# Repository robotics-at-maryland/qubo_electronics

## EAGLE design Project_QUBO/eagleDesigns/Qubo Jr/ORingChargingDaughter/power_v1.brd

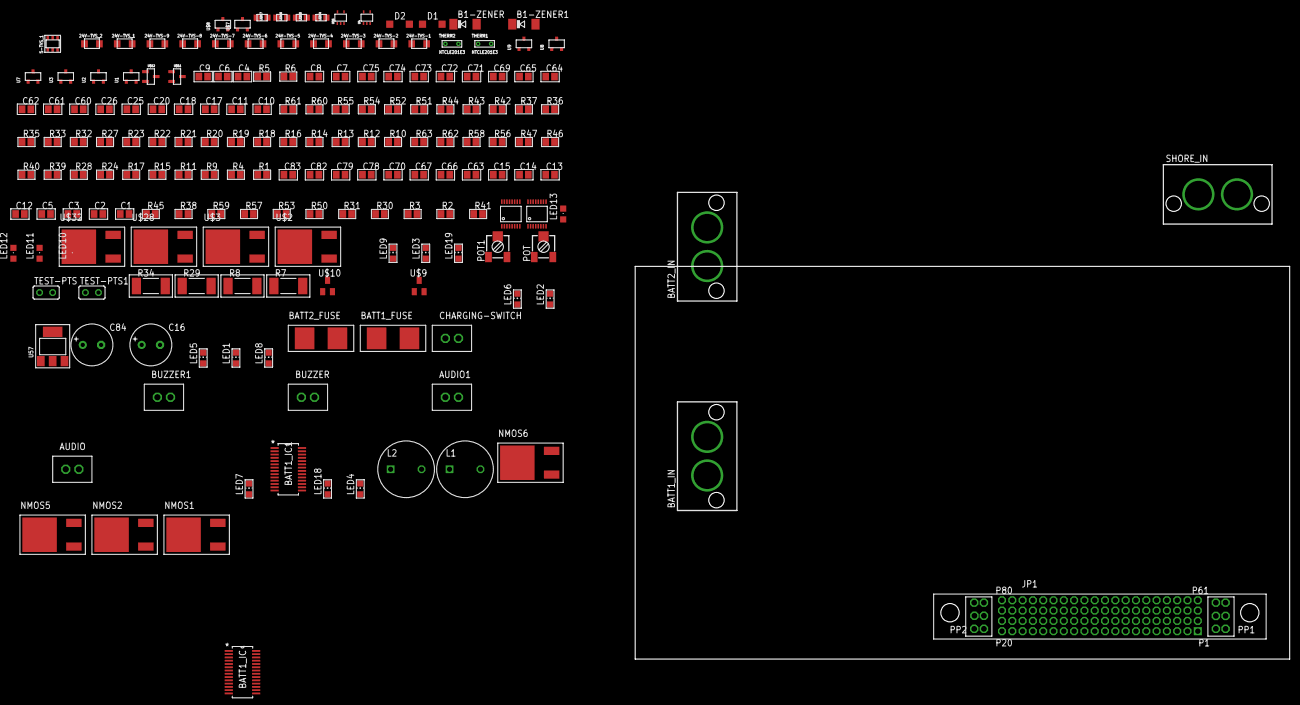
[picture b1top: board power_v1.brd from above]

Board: 2 copper layers, 127.0 x 76.2 mm, 181 parts (0 on the bottom side), 115 nets, no tracks yet.

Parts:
5-TVS_1: BZA408B; SOT457
24V-TVS-1, 24V-TVS-2, 24V-TVS-3, 24V-TVS-4, 24V-TVS-5, 24V-TVS-6, 24V-TVS-7, 24V-TVS-8, 24V-TVS-9, 24V-TVS_1, 24V-TVS_2: VTVS; DO-219AB
AUDIO, AUDIO1: KK254_VERT_2PIN22-29-2021; KK254_VERT_2PIN
B1-ZENER, B1-ZENER1: SOD106-R
BATT1_FUSE, BATT2_FUSE: 4A; 154-OMNI-BLOK
BATT1_IC, BATT1_IC1: MAX1737; QSOP28
BATT1_IN, BATT2_IN: 2_SUPERSABRE; SUPERSABRE_2CIRCUIT
BUZZER, BUZZER1: KK254_VERT_2PIN22-29-2021; KK254_VERT_2PIN
C1, C5, C12, C13, C14, C15, C63, C70, C78, C79, C82, C83: 0.1u; C0805
C2, C3, C66, C67: 2.2u; C0805
C4, C60, C69: 1u; C0805
C6, C9, C10, C71, C74, C75: 1n; C0805
C7, C8, C17, C64, C72, C73: 47n; C0805
C11, C20, C25, C26: 0.1; C0805
C16, C84: 120u; E3,5-8
C18, C65: 22u; C0805
C61, C62: 10u; C0805
CHARGING-SWITCH: KK254_VERT_2PIN22-29-2021; KK254_VERT_2PIN
D1, D2: SOD123
JP1: MPSC-01-80
L1, L2: 10uH; L6100
LED1, LED5: FASTCHG; CHIP-LED0805
LED2, LED6: FULLCHG; CHIP-LED0805
LED3, LED9: FAULT; CHIP-LED0805
LED4, LED18: Batt Connect.; CHIP-LED0805
LED7: Shore Power; CHIP-LED0805
LED8: CHARGING; CHIP-LED0805
LED10, LED11: Red; CHIPLED_0805
LED12, LED13: CHIPLED_0805
LED14, LED15: Blue; 0805
LED16, LED17: Green; 0805
LED19: ORING; CHIP-LED0805
NMOS1, NMOS2, NMOS5, NMOS6: STD95N2LH5; DPAK
POT, POT1: 10k; RTRIM3314J
R1, R4: 2-3k; R0805
R2, R3, R30, R31: ~50k; R0805
R5, R32: 10k; R0805
R6, R33, R52, R55, R60, R61: 330; R0805
R7, R8, R29, R34: 100m; R2512
R9, R11, R15, R17, R56, R58: 1.2k; R0805
R10, R12, R14, R16, R18, R20: 50k; R0805
R13, R21, R23: 510; R0805
R19, R22: 680; R0805
R24: 6.8k; R0805
R27: 12k; R0805
R28, R62, R63: 1.5k; R0805
R35, R42: 51k; R0805
R36, R43: 5m; R0805
R37, R44: 10\; R0805
R38, R45: 200k; R0805
R39, R46: 8.2k; R0805
R40, R47: 5.1k; R0805
R41: 20.8k; R0805
R50, R53, R57, R59: 20k+; R0805
R51, R54: 430; R0805
SHORE_IN: 2_SUPERSABRE; SUPERSABRE_2CIRCUIT
TEST-PTS, TEST-PTS1: 0; V526-0
THERM1, THERM2: NTCLE201E3; 2-0.3MM-LEADS
U1, U2, U3, U7, U8, U9: SSM3J353F; SOT-346-3/S-MINI
U4, U56: 74LVC1G14; TSSOP5
U57: NCP1117; SOT-223
U$1, U$27: LTC4364MSOP; MSOP16
U$2, U$3, U$28, U$32: STD95N2LH5; DPAK
U$7, U$8: SSM3J353F; SOT-346-3/S-MINI
U$9, U$10: BSS138CT-NDSOT23; SOT23
U$11, U$12: TL431DBZ; SOT-23-3

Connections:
+5V: C11.1, C20.1, C62.1, R24.2, U4.P$5, U56.P$5, U57.P$2, U57.P$4
BATT1_P: 24V-TVS_2.P$2, BATT1_FUSE.P$1, BATT1_IN.P$1
BATT2_P: 24V-TVS-3.P$2, BATT2_FUSE.P$1, BATT2_IN.P$1
BATT_1: BATT1_FUSE.P$2, BATT1_IC.7, C83.1, C84.+, R29.1, R34.1
BATT_2: BATT1_IC1.7, BATT2_FUSE.P$2, C15.1, C16.+, R7.1, R8.1
CCI_1: BATT1_IC.11, C72.1
CCI_2: BATT1_IC1.11, C7.1
CCS_1: BATT1_IC.10, C73.1
CCS_2: BATT1_IC1.10, C8.1
CCV_1: BATT1_IC.9, C71.1, R32.2
CCV_2: BATT1_IC1.9, C6.1, R5.2
CHARGE1_!FASTCHG!: BATT1_IC.16, R10.1, U7.P$1
CHARGE1_!FAULT!: BATT1_IC.15, R14.1, U9.P$1
CHARGE1_!FULLCHG!: BATT1_IC.17, R12.1, U8.P$1
CHARGE2_!FASTCHG!: BATT1_IC1.16, R16.1, U1.P$1
CHARGE2_!FAULT!: BATT1_IC1.15, R20.1, U3.P$1
CHARGE2_!FULLCHG!: BATT1_IC1.17, R18.1, U2.P$1
CHARGE-SWT: 5-TVS_1.P$1, CHARGING-SWITCH.P$1, R23.1, R24.1
CHARGE_!SHDN!: BATT1_IC.18, BATT1_IC1.18, R33.2, U4.P$2, U56.P$4
DCIN_1: B1-ZENER.C, BATT1_IC.26, BATT1_IC.27, BATT1_IC.28, C63.1, NMOS1.TAB
DCIN_2: B1-ZENER1.C, BATT1_IC1.26, BATT1_IC1.27, BATT1_IC1.28, C1.1, NMOS5.TAB
DHI1: BATT1_IC.25, NMOS1.1
DHI2: BATT1_IC1.25, NMOS5.1
DLO1: BATT1_IC.21, NMOS2.1
DLO2: BATT1_IC1.21, NMOS6.1
GND: 5-TVS_1.P$2, 24V-TVS-1.P$1, 24V-TVS-2.P$1, 24V-TVS-3.P$1, 24V-TVS-4.P$1, 24V-TVS-5.P$1, 24V-TVS-6.P$1, 24V-TVS-7.P$1, 24V-TVS-8.P$1, 24V-TVS-9.P$1, 24V-TVS_1.P$1, 24V-TVS_2.P$1, AUDIO.P$2, AUDIO1.P$2, BATT1_IC.6, BATT1_IC1.6, BATT1_IN.P$2, BATT2_IN.P$2, BUZZER.P$2, BUZZER1.P$2, C1.2, C2.2, C3.2, C4.2, C5.2, C6.2, C7.2, C8.2, C9.2, C10.2, C11.2, C13.2, C14.2, C15.2, C16.-, C17.2, C18.2, C20.2, C25.2, C26.2, C60.2, C61.2, C62.2, C63.2, C64.2, C65.2, C66.2, C67.2, C69.2, C70.2, C71.2, C72.2, C73.2, C74.2, C75.2, C79.2, C82.2, C83.2, C84.-, CHARGING-SWITCH.P$2, JP1.P1,1, JP1.P1,2, JP1.P1,3, JP1.P1,4, JP1.P1,5, JP1.P1,6, JP1.P2,1, JP1.P2,2, JP1.P2,3, JP1.P2,4, JP1.P2,5, JP1.P2,6, LED1.C, LED2.C, LED3.C, LED4.C, LED5.C, LED6.C, LED7.C, LED8.C, LED9.C, LED10.C, LED11.C, LED14.P$2, LED15.P$2, LED16.P$2, LED17.P$2, LED18.C, LED19.C, POT.1, POT1.1, R3.1, R27.1, R31.1, R40.1, R41.1, R47.1, SHORE_IN.P$2, TEST-PTS.1, TEST-PTS1.1, THERM1.P$2, THERM2.P$2, U4.P$3, U56.P$3, U57.P$1, U$1.GND, U$1.OV, U$9.2, U$10.2, U$11.P$3, U$12.P$3, U$27.GND, U$27.OV
LIN_1: L1.P$1, NMOS1.3, NMOS2.TAB
LIN_2: L2.P$1, NMOS5.3, NMOS6.TAB
LOUT_1: BATT1_IC.19, C82.1, L1.P$2, R29.2, R34.2
LOUT_2: BATT1_IC1.19, C14.1, L2.P$2, R7.2, R8.2
unnamed: LED4.A, R1.1
unnamed: LED1.A, R9.1
unnamed: BATT1_IC.20, NMOS2.3
unnamed: C5.1, R5.1
unnamed: BATT1_IC1.24, C12.1
unnamed: BATT1_IC1.23, C12.2, D2.C
unnamed: BATT1_IC1.22, C13.1, D2.A
unnamed: LED5.A, R15.1
unnamed: R15.2, U1.P$2
unnamed: LED6.A, R17.1
unnamed: R17.2, U2.P$2
unnamed: LED3.A, R13.1
unnamed: LED9.A, R21.1
unnamed: BUZZER1.P$1, R21.2, R22.1
unnamed: R22.2, U3.P$2
unnamed: BATT1_IC1.20, NMOS6.3
unnamed: R35.2, R39.1
unnamed: U$27.SOURCE, U$28.3, U$32.3
unnamed: R41.2, R45.1, U$1.UV
unnamed: R42.1, R47.2, U$1.FB
unnamed: R44.1, U$1.HGATE
unnamed: LED2.A, R11.1
unnamed: R9.2, U7.P$2
unnamed: C17.1, U$1.TMR
unnamed: R42.2, R46.1
unnamed: R11.2, U8.P$2
unnamed: R44.2, U$2.1
unnamed: U$1.SOURCE, U$2.3, U$3.3
unnamed: BUZZER.P$1, R13.2, R19.1
unnamed: R19.2, U9.P$2
unnamed: R43.1, U$1.SENSE, U$3.TAB
unnamed: U$1.DGATE, U$3.1
unnamed: LED7.A, R28.1
unnamed: R37.1, U$27.HGATE
unnamed: LED18.A, R4.1
unnamed: R27.2, R38.1, U$27.UV
unnamed: LED10.A, R51.1
unnamed: LED19.A, R6.1
unnamed: R52.2, U$7.P$3
unnamed: AUDIO.P$1, R51.2, R52.1
unnamed: LED11.A, R54.1
unnamed: R55.2, U$8.P$3
unnamed: C60.1, R23.2, U56.P$2
unnamed: R35.1, R40.2, U$27.FB
unnamed: C64.1, U$27.TMR
unnamed: AUDIO1.P$1, R54.2, R55.1
unnamed: R56.1, U$9.3
unnamed: LED8.A, R33.1
unnamed: LED12.C, R56.2
unnamed: R37.2, U$28.1
unnamed: R36.1, U$27.SENSE, U$32.TAB
unnamed: U$27.DGATE, U$32.1
unnamed: R58.1, U$10.3
unnamed: LED13.C, R58.2
unnamed: C70.1, R32.1
unnamed: POT.2, TEST-PTS.2, U$11.P$2
unnamed: LED14.P$1, R60.1, U$11.P$1
unnamed: POT1.2, TEST-PTS1.2, U$12.P$2
unnamed: LED15.P$1, R61.1, U$12.P$1
unnamed: LED16.P$1, R62.1
unnamed: LED17.P$1, R63.1
unnamed: BATT1_IC.24, C78.1
unnamed: BATT1_IC.23, C78.2, D1.C
unnamed: BATT1_IC.22, C79.1, D1.A
ORING1_!FAULT!: R50.1, U$1.FLT, U$7.P$1
ORING2_!FAULT!: R53.1, U$8.P$1, U$27.FLT
ORING2_ENOUT: R57.1, U$9.1, U$27.ENOUT
ORING_!SHDN!: R6.2, U4.P$4, U$1.SHDN, U$27.SHDN
ORING_ENOUT: R59.1, U$10.1
REF_1: BATT1_IC.2, BATT1_IC.3, BATT1_IC.5, C69.1, R30.1
REF_2: BATT1_IC1.2, BATT1_IC1.3, BATT1_IC1.5, C4.1, R2.1
THM1: BATT1_IC.4, THERM1.P$1
THM2: BATT1_IC1.4, THERM2.P$1
TIMER1_1: BATT1_IC.13, C74.1
TIMER1_2: BATT1_IC1.13, C9.1
TIMER2_1: BATT1_IC.14, C75.1
TIMER2_2: BATT1_IC1.14, C10.1
VADJ_1: BATT1_IC.8, R30.2, R31.2
VADJ_2: BATT1_IC1.8, R2.2, R3.2
VL_1: BATT1_IC.1, BATT1_IC.12, C66.1, C67.1
VL_2: BATT1_IC1.1, BATT1_IC1.12, C2.1, C3.1
V_BATT: 24V-TVS-6.P$2, 24V-TVS-7.P$2, 24V-TVS-8.P$2, 24V-TVS-9.P$2, C18.1, C65.1, JP1.1, JP1.2, JP1.3, JP1.4, JP1.5, JP1.6, JP1.7, JP1.8, JP1.9, JP1.10, JP1.21, JP1.22, JP1.23, JP1.24, JP1.25, JP1.26, JP1.27, JP1.28, JP1.29, JP1.30, JP1.41, JP1.42, JP1.43, JP1.44, JP1.45, JP1.46, JP1.47, JP1.48, JP1.49, JP1.50, JP1.61, JP1.62, JP1.63, JP1.64, JP1.65, JP1.66, JP1.67, JP1.68, JP1.69, JP1.70, R36.2, R39.2, R43.2, R46.2, U$1.OUT, U$27.OUT
V_BATT1: C25.1, C61.1, LED12.A, POT1.3, R1.2, R45.2, R53.2, R57.2, R61.2, R63.2, U57.P$3, U$1.VCC, U$2.TAB, U$8.P$2
V_BATT2: C26.1, LED13.A, POT.3, R4.2, R38.2, R50.2, R59.2, R60.2, R62.2, U$7.P$2, U$27.VCC, U$28.TAB
V_SHORE: 24V-TVS-1.P$2, 24V-TVS-2.P$2, 24V-TVS-4.P$2, 24V-TVS-5.P$2, 24V-TVS_1.P$2, B1-ZENER.A, B1-ZENER1.A, JP1.11, JP1.12, JP1.13, JP1.14, JP1.15, JP1.16, JP1.17, JP1.18, JP1.19, JP1.20, JP1.31, JP1.32, JP1.33, JP1.34, JP1.35, JP1.36, JP1.37, JP1.38, JP1.39, JP1.40, JP1.51, JP1.52, JP1.53, JP1.54, JP1.55, JP1.56, JP1.57, JP1.58, JP1.59, JP1.60, JP1.71, JP1.72, JP1.73, JP1.74, JP1.75, JP1.76, JP1.77, JP1.78, JP1.79, JP1.80, R10.2, R12.2, R14.2, R16.2, R18.2, R20.2, R28.2, SHORE_IN.P$1, U1.P$3, U2.P$3, U3.P$3, U7.P$3, U8.P$3, U9.P$3

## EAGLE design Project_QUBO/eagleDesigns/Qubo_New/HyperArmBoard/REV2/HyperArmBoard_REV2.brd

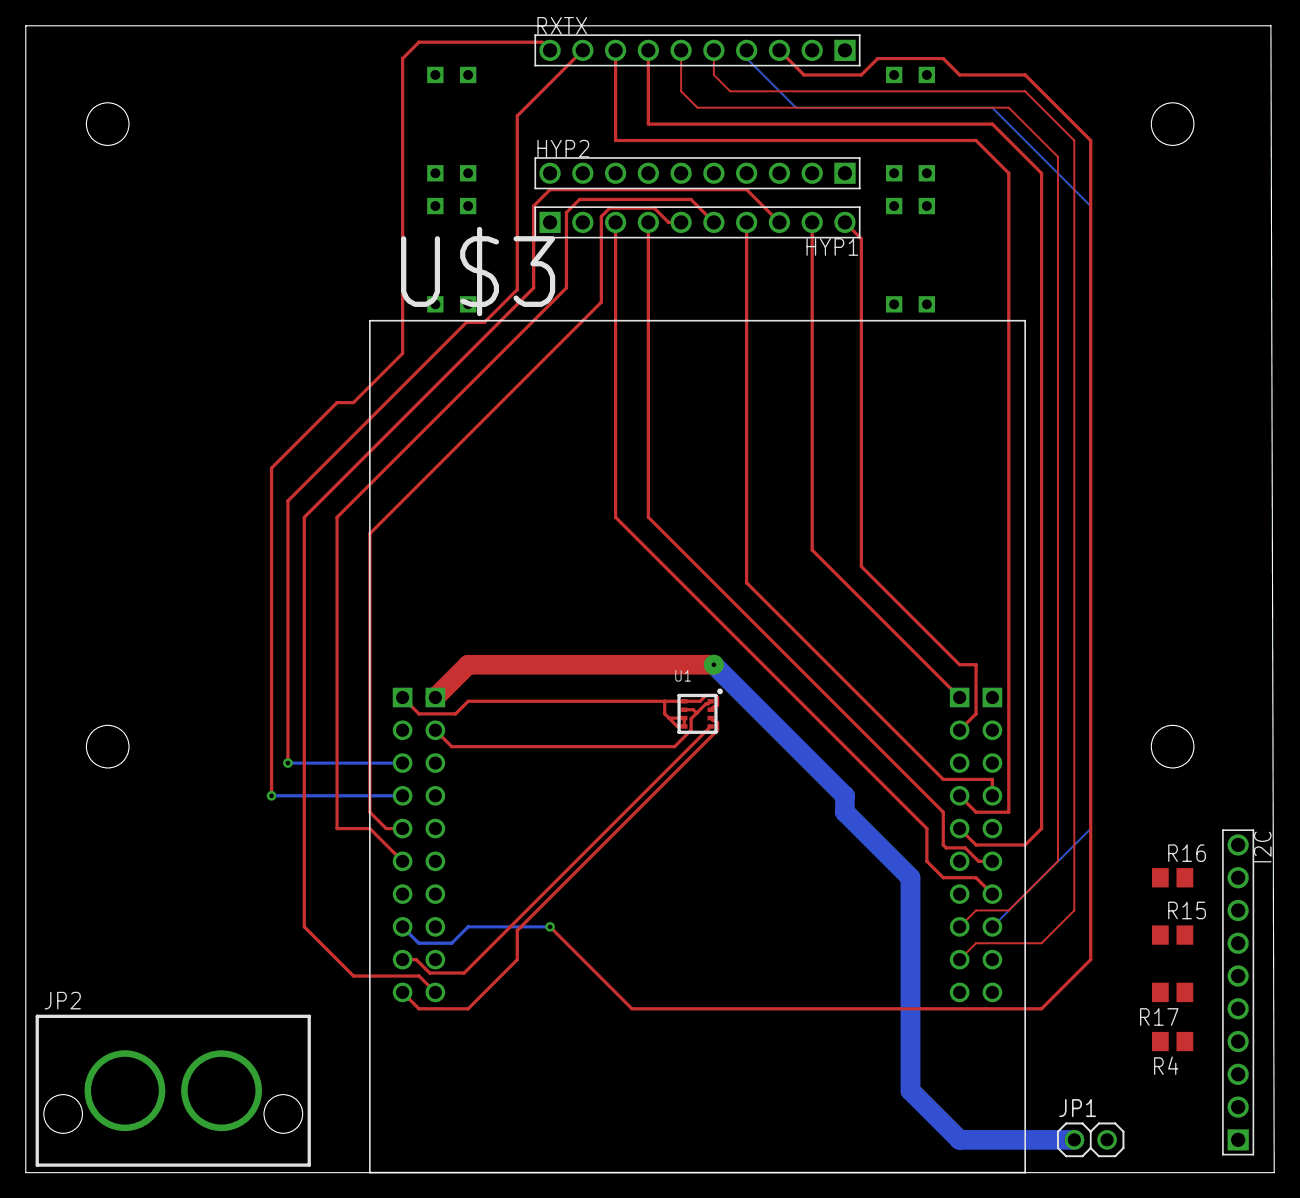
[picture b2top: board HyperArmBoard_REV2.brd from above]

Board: 2 copper layers, 96.8 x 88.9 mm, 16 parts (0 on the bottom side), 24 nets.

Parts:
HYP1, HYP2: KK254_10-PIN
I2C: KK254_10-PIN
JP1: 1X02
JP2: PWR; SUPERSABRE_2CIRCUIT
R4, R15, R16, R17: 5k; R0805
RXTX: KK254_10-PIN
U1: BME280; BME280_LGA
U$3: TIVA-C_EVAL
U$4, U$5, U$6, U$7: BCS-106-L-D-PE-BE; 4-PIN-BIGPOWER

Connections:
3.3V: I2C.P$9, R15.1, R16.1, U1.P$2, U1.P$5, U1.P$6, U1.P$8, U$3.1-1
5V: JP1.1, R4.2, R17.2, U$3.3-1
BIGVIN: JP2.P$1, U$4.P$1, U$4.P$2, U$4.P$3, U$4.P$4, U$5.P$1, U$5.P$2, U$5.P$3, U$5.P$4
DGND: I2C.P$10, JP1.2, JP2.P$2, U1.P$1, U1.P$7, U$3.2-1, U$3.3-2, U$6.P$1, U$6.P$2, U$6.P$3, U$6.P$4, U$7.P$1, U$7.P$2, U$7.P$3, U$7.P$4
MISO_0: RXTX.P$4, U$3.2-8
MOSI_0: RXTX.P$3, U$3.1-8
PWM0: HYP1.P$3, U$3.2-7
PWM1: HYP1.P$4, U$3.2-6
PWM2: HYP1.P$5, U$3.1-5
PWM3: HYP1.P$6, U$3.1-6
PWM4: HYP1.P$7, U$3.2-4
PWM5: HYP1.P$8, U$3.3-10
PWM6: HYP1.P$9, U$3.4-1
PWM7: HYP1.P$10, U$3.4-2
RX_MC: RXTX.P$8, U$3.4-4
RX_MD: RXTX.P$6, U$3.4-8
RX_MF: RXTX.P$9, U$3.1-3
SCL_0: I2C.P$5, R4.1, U$3.2-2
SCL_1: I2C.P$7, R15.2, U1.P$4, U$3.1-9
SDA_0: I2C.P$6, R17.1, U$3.4-3
SDA_1: I2C.P$8, R16.2, U1.P$3, U$3.1-10
TX_MC: RXTX.P$7, U$3.4-5
TX_MD: RXTX.P$5, U$3.4-9
TX_MF: RXTX.P$10, U$3.1-4

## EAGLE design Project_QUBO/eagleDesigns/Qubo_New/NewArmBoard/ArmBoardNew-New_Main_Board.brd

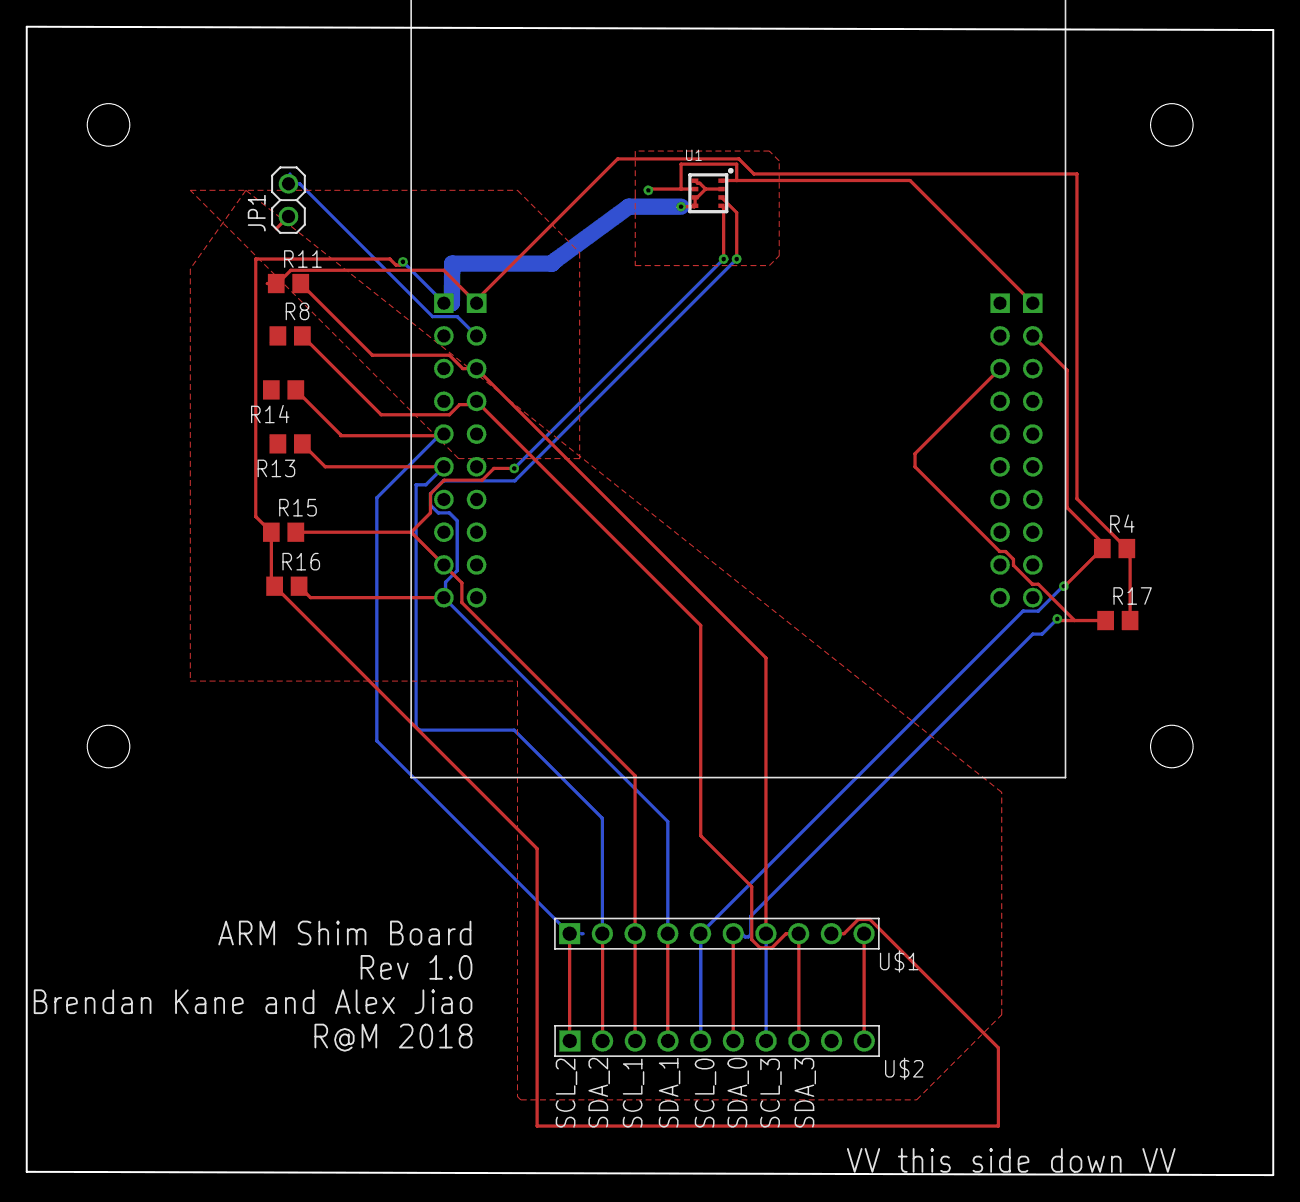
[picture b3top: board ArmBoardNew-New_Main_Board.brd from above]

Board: 2 copper layers, 96.8 x 89.2 mm, 13 parts (0 on the bottom side), 12 nets.

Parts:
JP1: 1X02
R4, R8, R11, R13, R14, R15, R16, R17: 5k; R0805
U1: BME280; BME280_LGA
U$1, U$2: KK254_10-PIN
U$3: TIVA-C_EVAL

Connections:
3.3V: R15.1, R16.1, U1.P$2, U1.P$5, U1.P$6, U1.P$8, U$1.P$9, U$3.1-1
5V: JP1.1, R4.2, R8.1, R11.1, R13.2, R14.2, R17.2, U$3.3-1
DGND: JP1.2, U1.P$1, U1.P$7, U$3.2-1, U$3.3-2
unnamed: U$1.P$10, U$2.P$10
SCL_0: R4.1, U$1.P$5, U$2.P$5, U$3.2-2
SCL_1: R15.2, U1.P$4, U$1.P$3, U$2.P$3, U$3.1-9
SCL_2: R14.1, U$1.P$1, U$2.P$1, U$3.1-5
SCL_3: R11.2, U$1.P$7, U$2.P$7, U$3.3-3
SDA_0: R17.1, U$1.P$6, U$2.P$6, U$3.4-3
SDA_1: R16.2, U1.P$3, U$1.P$4, U$2.P$4, U$3.1-10
SDA_2: R13.1, U$1.P$2, U$2.P$2, U$3.1-6
SDA_3: R8.2, U$1.P$8, U$2.P$8, U$3.3-4

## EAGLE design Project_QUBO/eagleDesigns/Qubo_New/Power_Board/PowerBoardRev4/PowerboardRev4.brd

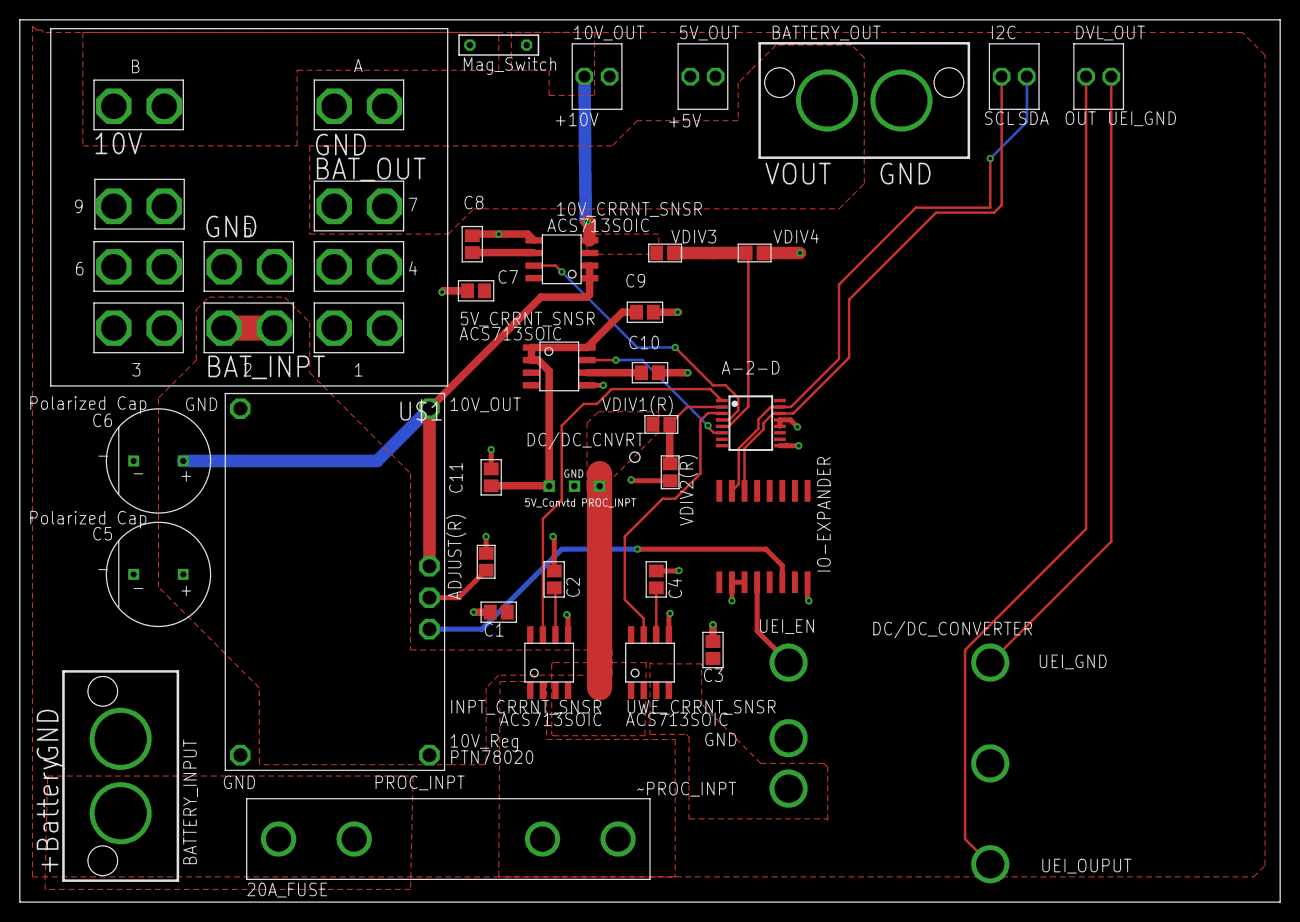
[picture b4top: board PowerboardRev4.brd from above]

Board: 2 copper layers, 127.0 x 88.9 mm, 34 parts (0 on the bottom side), 28 nets.

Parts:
5V_CRRNT_SNSR, 10V_CRRNT_SNSR: ACS713SOIC; ACS713-SOIC
5V_OUT, 10V_OUT: KK254_VERT_2PIN""; KK254_VERT_2PIN
10V_REGULATOR: PTN78020; PTN
20A_FUSE: 1.25"_FUSECLIPS
A-2-D: ADS7828; TSSOP16
ADJUST(R): 2.66k; R0805
BATTERY_INPUT: 2_SUPERSABRE; SUPERSABRE_2CIRCUIT
BATTERY_OUT: 2_SUPERSABRE; SUPERSABRE_2CIRCUIT
C1, C3, C7, C9: 0.1u; C0805
C2, C4, C8, C10: 47n; C0805
C5, C6: PANASONIC_A_TYPE_M
C11: FILTER; C0805
DC/DC_CNVRT: TSR2-2450; TSR2
DC/DC_CONVERTER: UEI15
DVL_OUT: KK254_VERT_2PIN""; KK254_VERT_2PIN
I2C: KK254_VERT_2PIN""; KK254_VERT_2PIN
INPT_CRRNT_SNSR: ACS713SOIC; ACS713-SOIC
IO-EXPANDER: PCF8574T; SO16W
MAGREAD: HE151TR-ND
U$1: KUHP-5XX1-XX; KUHP_6.35MM-QUICK-CONNECT
UWE_CRRNT_SNSR: ACS713SOIC; ACS713-SOIC
VDIV1(R), VDIV3: 90kO; R0805
VDIV2(R), VDIV4: 10kO; R0805

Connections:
5V: 5V_CRRNT_SNSR.P$3, 5V_CRRNT_SNSR.P$4, 5V_OUT.P$2, 10V_CRRNT_SNSR.P$8, A-2-D.10, A-2-D.16, C1.2, C3.2, C7.2, INPT_CRRNT_SNSR.P$8, IO-EXPANDER.1, IO-EXPANDER.16, UWE_CRRNT_SNSR.P$8
5V_CNVTD: 5V_CRRNT_SNSR.P$1, 5V_CRRNT_SNSR.P$2, 5V_CRRNT_SNSR.P$8, C9.2, C11.1, DC/DC_CNVRT.3
5V_CURRENT: 5V_CRRNT_SNSR.P$7, A-2-D.6
5V_FILT: 5V_CRRNT_SNSR.P$6, C10.2
10V_CURRENT: 10V_CRRNT_SNSR.P$7, A-2-D.4
10V_EN: 10V_REGULATOR.INHIBIT, IO-EXPANDER.6
10V_OUT: 10V_CRRNT_SNSR.P$1, 10V_CRRNT_SNSR.P$2, 10V_REGULATOR.SENSE, 10V_REGULATOR.VOUT, C6.+
10V_VOLTAGE: A-2-D.5, VDIV3.2, VDIV4.1
+VIN: DC/DC_CONVERTER.+VIN, UWE_CRRNT_SNSR.P$3, UWE_CRRNT_SNSR.P$4
BATTERY_LINE: BATTERY_OUT.P$2, U$1.7A, U$1.7B
FILTER: C4.2, UWE_CRRNT_SNSR.P$6
FLTR_10V: 10V_CRRNT_SNSR.P$6, C8.2
GND: 5V_CRRNT_SNSR.P$5, 5V_OUT.P$1, 10V_CRRNT_SNSR.P$5, 10V_OUT.P$1, 10V_REGULATOR.GND1, 10V_REGULATOR.GND2, A-2-D.9, A-2-D.12, A-2-D.13, ADJUST(R).2, BATTERY_INPUT.P$1, BATTERY_OUT.P$1, C1.1, C2.1, C3.1, C4.1, C5.-, C6.-, C7.1, C8.1, C9.1, C10.1, C11.2, DC/DC_CNVRT.2, DC/DC_CONVERTER.-VIN, INPT_CRRNT_SNSR.P$5, IO-EXPANDER.2, IO-EXPANDER.3, IO-EXPANDER.8, U$1.5A, U$1.5B, U$1.AA, U$1.AB, UWE_CRRNT_SNSR.P$5, VDIV2(R).2, VDIV4.2
INPT_FILT: C2.2, INPT_CRRNT_SNSR.P$6
INPUT_CURRENT: A-2-D.1, INPT_CRRNT_SNSR.P$7
INPUT_VOLTAGE: A-2-D.2, VDIV1(R).2, VDIV2(R).1
unnamed: 10V_REGULATOR.ADJUST, ADJUST(R).1
PROCESSED_10V_OUT: 10V_CRRNT_SNSR.P$3, 10V_CRRNT_SNSR.P$4, 10V_OUT.P$2, MAGREAD.P$1, VDIV3.1
PROCESSED_UEI_OUTPUT: DC/DC_CONVERTER.+VOUT, DVL_OUT.P$2
PROC_INPUT: 10V_REGULATOR.VIN, C5.+, DC/DC_CNVRT.1, INPT_CRRNT_SNSR.P$3, INPT_CRRNT_SNSR.P$4, U$1.2A, U$1.2B, UWE_CRRNT_SNSR.P$1, UWE_CRRNT_SNSR.P$2, VDIV1(R).1
RLY_10V: MAGREAD.P$2, U$1.BA, U$1.BB
SCL: A-2-D.14, I2C.P$2, IO-EXPANDER.14
SDA: A-2-D.15, I2C.P$1, IO-EXPANDER.15
UEI_EN: DC/DC_CONVERTER.ON/OFFCNTRL, IO-EXPANDER.4
UEI_GND: DC/DC_CONVERTER.-VOUT, DVL_OUT.P$1
UWE_CURRENT: A-2-D.3, UWE_CRRNT_SNSR.P$7
VBAT: 20A_FUSE.P$1, 20A_FUSE.P$2, BATTERY_INPUT.P$2
VBAT_P: 20A_FUSE.P$3, 20A_FUSE.P$4, INPT_CRRNT_SNSR.P$1, INPT_CRRNT_SNSR.P$2
